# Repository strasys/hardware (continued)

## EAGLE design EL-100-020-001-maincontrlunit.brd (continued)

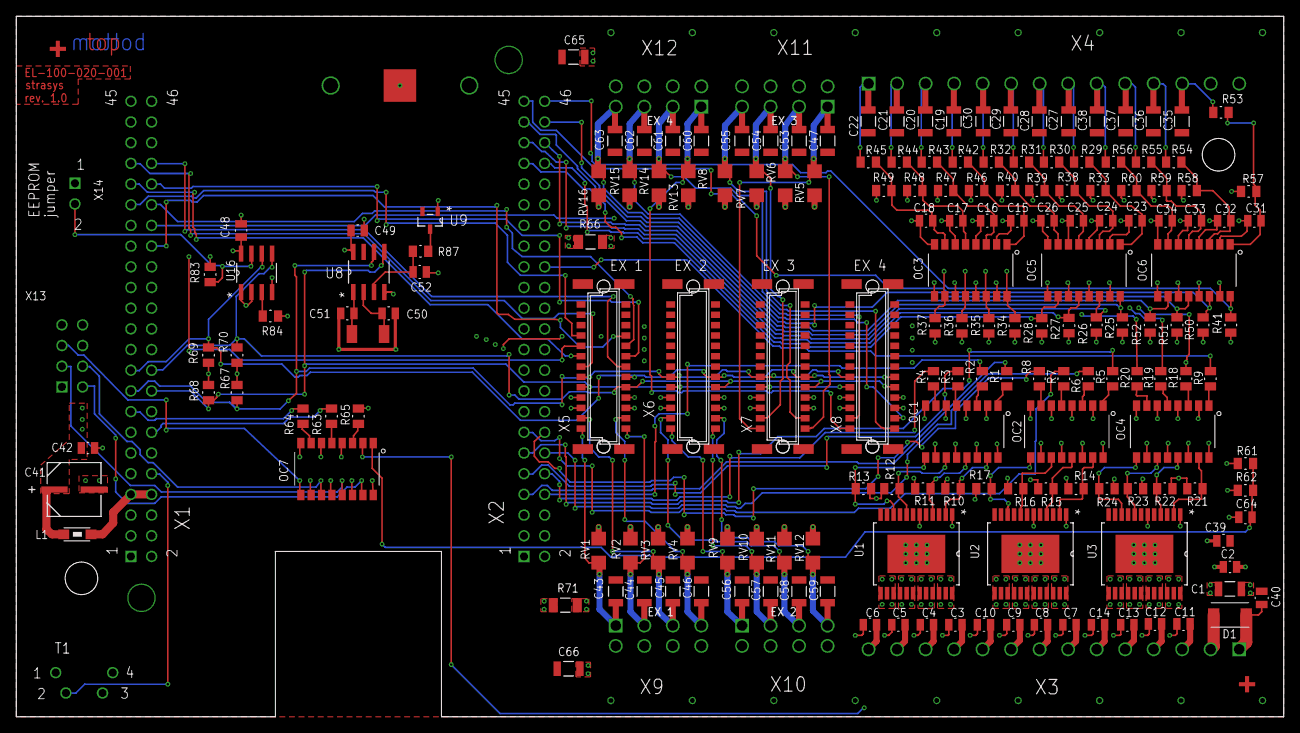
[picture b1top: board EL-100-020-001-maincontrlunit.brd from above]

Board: 4 copper layers, 155.6 x 86.0 mm, 190 parts (0 on the bottom side), 138 nets.

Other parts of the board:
U$1, U$2: PASSER_SMD4

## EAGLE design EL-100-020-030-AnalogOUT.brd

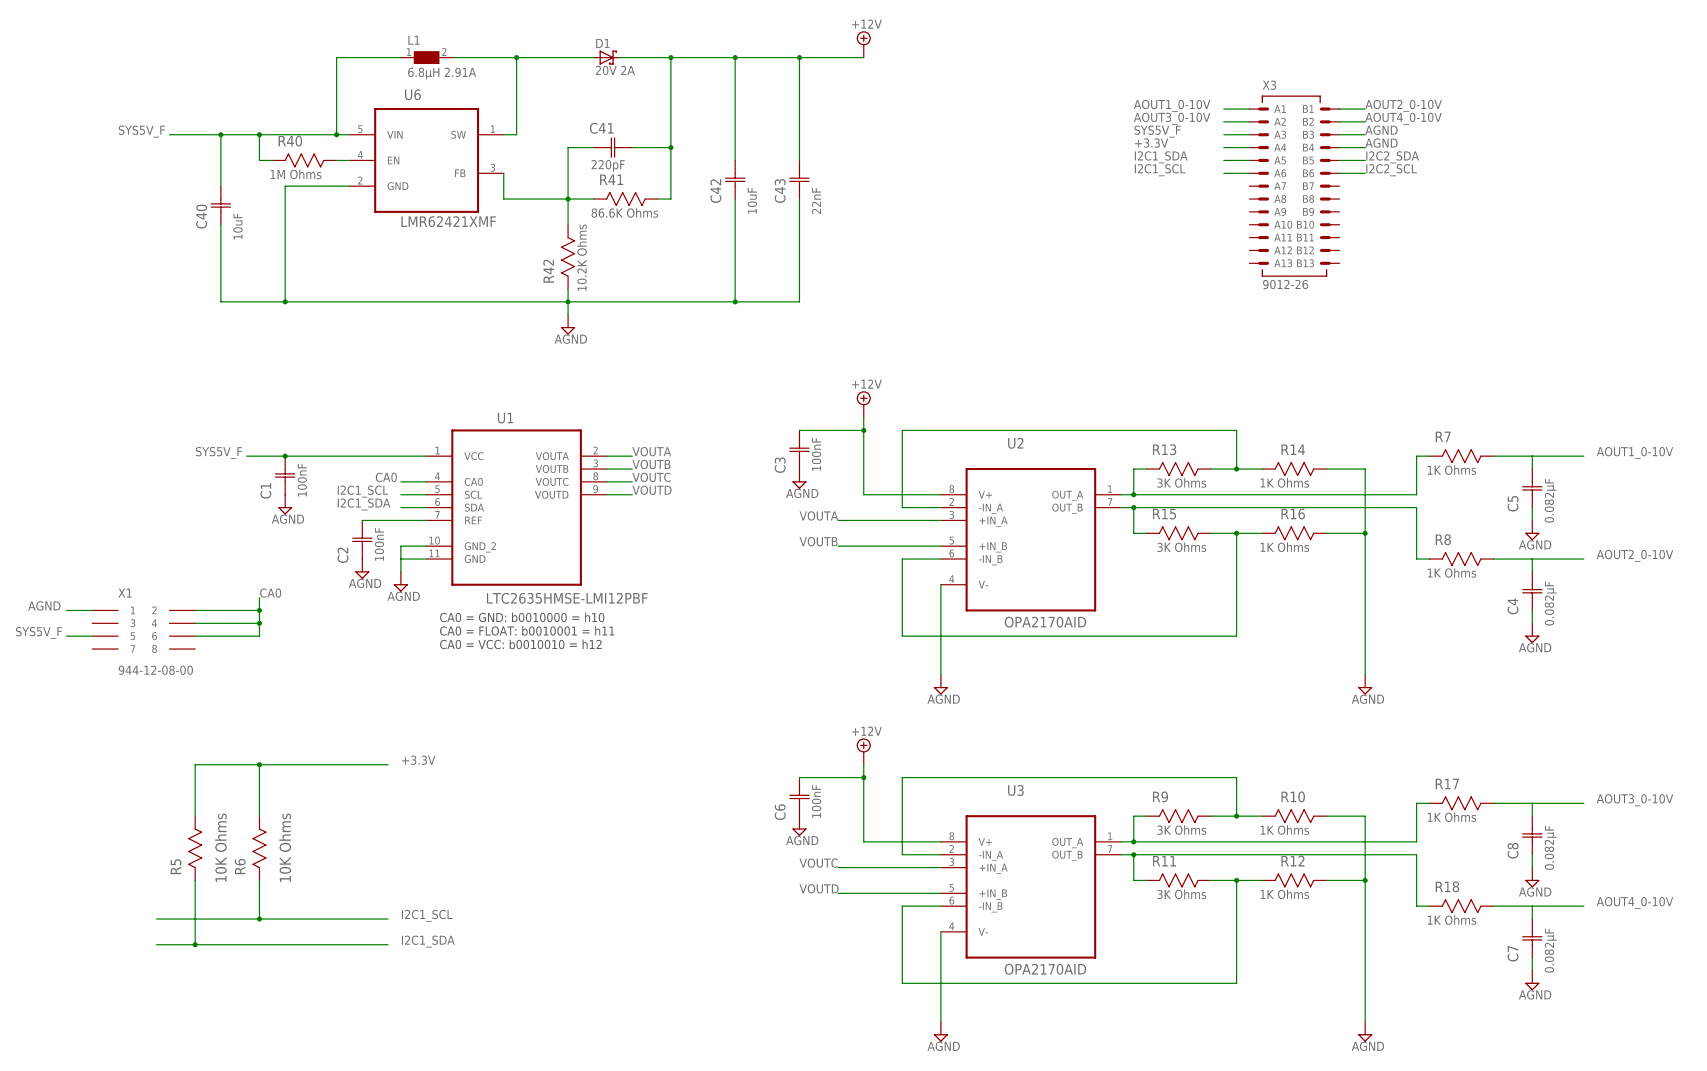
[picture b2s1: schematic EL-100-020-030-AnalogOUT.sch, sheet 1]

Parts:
C1, C2, C3, C6: 100nF; CAPC2013X110N
C4, C5, C7, C8: 0.082µF; CAPC2013X88N; TOLERANCE ±10%; MPN MC0805B823K500CT
C40: 10uF; CAPC2013X140N
C41: 220pF; CAPC2013X88N
C42: 10uF; CAPC3216X180N
C43: 22nF; CAPC2013X88N
D1: 20V 2A; SMB
L1: 6.8µH 2.91A; WE-PD_7332/7345_PLASTIC_BASE
R5, R6: 10K Ohms; RESC2013X65N
R7, R8, R17, R18: 1K Ohms; RESC2013X65N
R9, R11, R13, R15: 3K Ohms; RESC2013X65N; TOLERANCE ±0.1%; MPN ERA6AEB302V
R10, R12, R14, R16: 1K Ohms; RESC2013X65N; TOLERANCE ±0.1%; MPN ERA6AEB102V
R40: 1M Ohms; RESC2013X65N
R41: 86.6K Ohms; RESC2013X65N
R42: 10.2K Ohms; RESC2013X65N
U1: LTC2635HMSE-LMI12PBF; SOP50P490X110-11N
U2, U3: OPA2170AID; SOIC127P600X175-8N
U6: LMR62421XMF; SOT95P290X145-5N
X1: 944-12-08-00; 2,54_2X8
X3: 9012-26

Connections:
+3.3V: R5.1, R6.1, X3.A4; also elsewhere on the board
+12V: C3.2 (C2), C6.2 (C2), C41.2 (C2), C42.2 (C2), C43.2 (C2), D1.C, R41.1, U2.8 (V+), U3.8 (V+)
AGND: C1.1 (C1), C2.1 (C1), C3.1 (C1), C4.1 (C1), C5.1 (C1), C6.1 (C1), C7.1 (C1), C8.1 (C1), C40.1 (C1), C42.1 (C1), C43.1 (C1), R10.1, R12.1, R14.1, R16.1, R42.2, U1.10 (GND_2), U1.11 (GND), U2.4 (V-), U3.4 (V-), U6.2 (GND), X1.P1 (1), X3.B3, X3.B4; also elsewhere on the board
AOUT1_0-10V: C5.2 (C2), R7.1, X3.A1
AOUT2_0-10V: C4.2 (C2), R8.1, X3.B1
AOUT3_0-10V: C8.2 (C2), R17.1, X3.A2
AOUT4_0-10V: C7.2 (C2), R18.1, X3.B2
CA0: U1.4 (CA0), X1.P2 (2), X1.P4 (4), X1.P6 (6)
FB_LMR62: C41.1 (C1), R41.2, R42.1, U6.3 (FB)
I2C1_SCL: R6.2, U1.5 (SCL), X3.A6
I2C1_SDA: R5.2, U1.6 (SDA), X3.A5
I2C2_SCL: X3.B6; also elsewhere on the board
I2C2_SDA: X3.B5; also elsewhere on the board
unnamed: C2.2 (C2), U1.7 (REF)
unnamed: R40.1, U6.4 (EN)
OPA21_-IN_A: R13.1, R14.2, U2.2 (-IN_A)
OPA21_-IN_A1: R9.1, R10.2, U3.2 (-IN_A)
OPA21_-IN_B: R15.1, R16.2, U2.6 (-IN_B)
OPA21_-IN_B1: R11.1, R12.2, U3.6 (-IN_B)
OPA21_AOUTB: R8.2, R15.2, U2.7 (OUT_B)
OPA21_AOUTB1: R11.2, R18.2, U3.7 (OUT_B)
OPA21_OUT_A: R7.2, R13.2, U2.1 (OUT_A)
OPA21_OUT_A1: R9.2, R17.2, U3.1 (OUT_A)
SW_LMR62: D1.A, L1.2, U6.1 (SW)
SYS5V_F: C1.2 (C2), C40.2 (C2), L1.1, R40.2, U1.1 (VCC), U6.5 (VIN), X1.P5 (5), X3.A3
VOUTA: U1.2 (VOUTA), U2.3 (+IN_A)
VOUTB: U1.3 (VOUTB), U2.5 (+IN_B)
VOUTC: U1.8 (VOUTC), U3.3 (+IN_A)
VOUTD: U1.9 (VOUTD), U3.5 (+IN_B)

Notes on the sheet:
CA0 = GND: b0010000 = h10 CA0 = FLOAT: b0010001 = h11 CA0 = VCC: b0010010 = h12

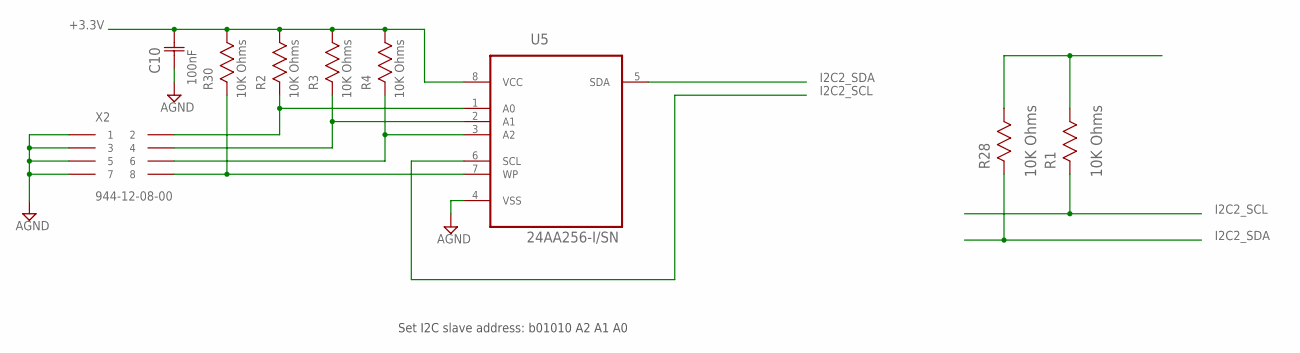
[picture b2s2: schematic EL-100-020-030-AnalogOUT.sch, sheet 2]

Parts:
C10: 100nF; CAPC2013X110N
R1, R2, R3, R4, R28, R30: 10K Ohms; RESC2013X65N
U5: 24AA256-I/SN; SOIC127P600X175-8N
X2: 944-12-08-00; 2,54_2X8

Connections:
24AA-A0: R2.2, U5.1 (A0), X2.P2 (2)
24AA_A1: R3.2, U5.2 (A1), X2.P4 (4)
24AA_A2: R4.2, U5.3 (A2), X2.P6 (6)
24AA_WP: R30.2, U5.7 (WP), X2.P8 (8)
+3.3V: C10.2 (C2), R1.1, R2.1, R3.1, R4.1, R28.1, R30.1, U5.8 (VCC); also elsewhere on the board
AGND: C10.1 (C1), U5.4 (VSS), X2.P1 (1), X2.P3 (3), X2.P5 (5), X2.P7 (7); also elsewhere on the board
I2C2_SCL: R1.2, U5.6 (SCL); also elsewhere on the board
I2C2_SDA: R28.2, U5.5 (SDA); also elsewhere on the board

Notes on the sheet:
Set I2C slave address: b01010 A2 A1 A0

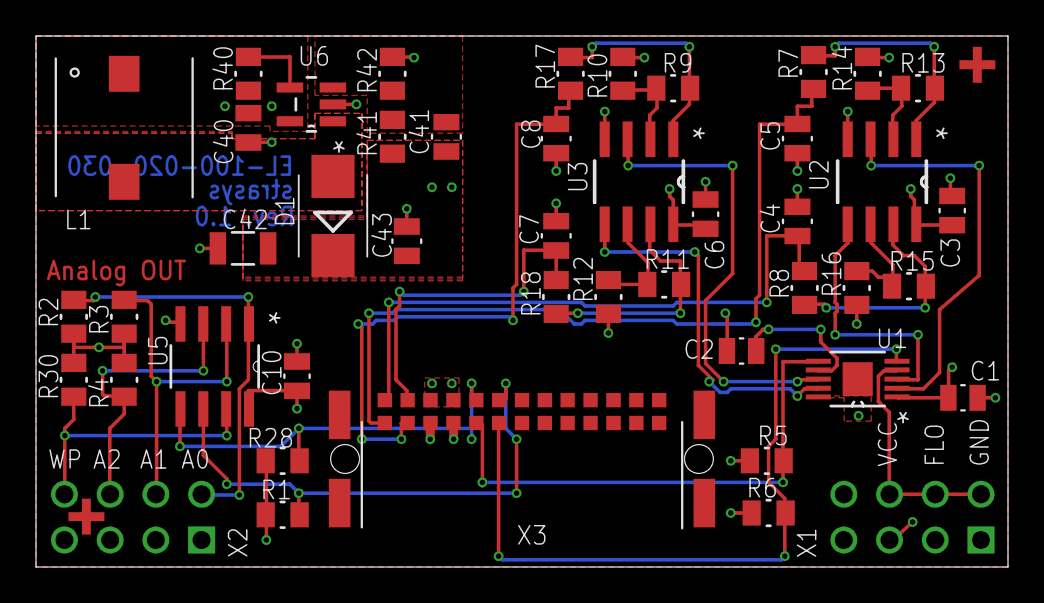
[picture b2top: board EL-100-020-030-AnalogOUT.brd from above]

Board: 4 copper layers, 54.0 x 29.5 mm, 48 parts (0 on the bottom side), 33 nets.

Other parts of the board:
U$1, U$2: PASSER_SMD4

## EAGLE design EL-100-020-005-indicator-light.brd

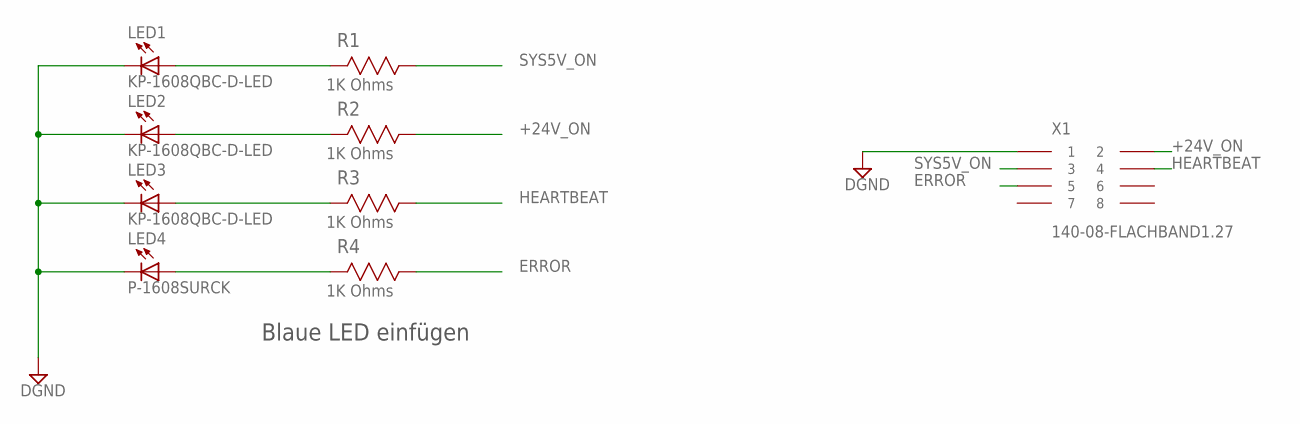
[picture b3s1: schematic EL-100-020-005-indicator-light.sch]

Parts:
LED1, LED2, LED3: KP-1608QBC-D-LED; KP-1608QBCD-D-LED
LED4: P-1608SURCK; KP-1608QBCD-D-LED
R1, R2, R3, R4: 1K Ohms; RESC2013X65N
X1: 140-08-FLACHBAND1.27; 2,54_2X8

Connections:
+24V_ON: R2.1, X1.P2 (2)
DGND: LED1.2, LED2.2, LED3.2, LED4.2, X1.P1 (1)
ERROR: R4.1, X1.P5 (5)
HEARTBEAT: R3.1, X1.P4 (4)
unnamed: LED1.1, R1.2
unnamed: LED2.1, R2.2
unnamed: LED3.1, R3.2
unnamed: LED4.1, R4.2
SYS5V_ON: R1.1, X1.P3 (3)

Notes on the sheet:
Blaue LED einfügen

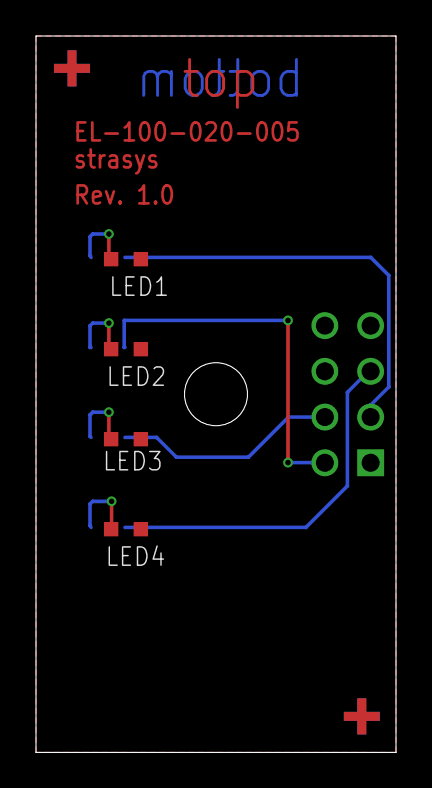
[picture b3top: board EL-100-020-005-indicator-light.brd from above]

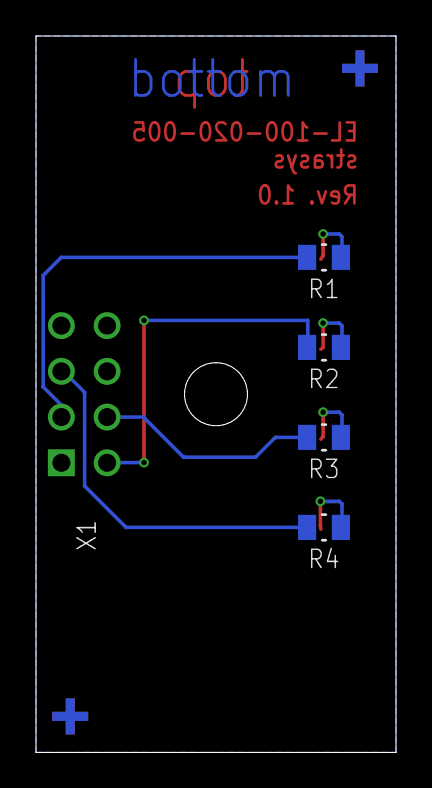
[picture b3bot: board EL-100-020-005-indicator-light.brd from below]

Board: 2 copper layers, 20.0 x 39.8 mm, 13 parts (7 on the bottom side), 9 nets.

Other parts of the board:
U$1, U$2, U$3, U$4: PASSER_SMD4

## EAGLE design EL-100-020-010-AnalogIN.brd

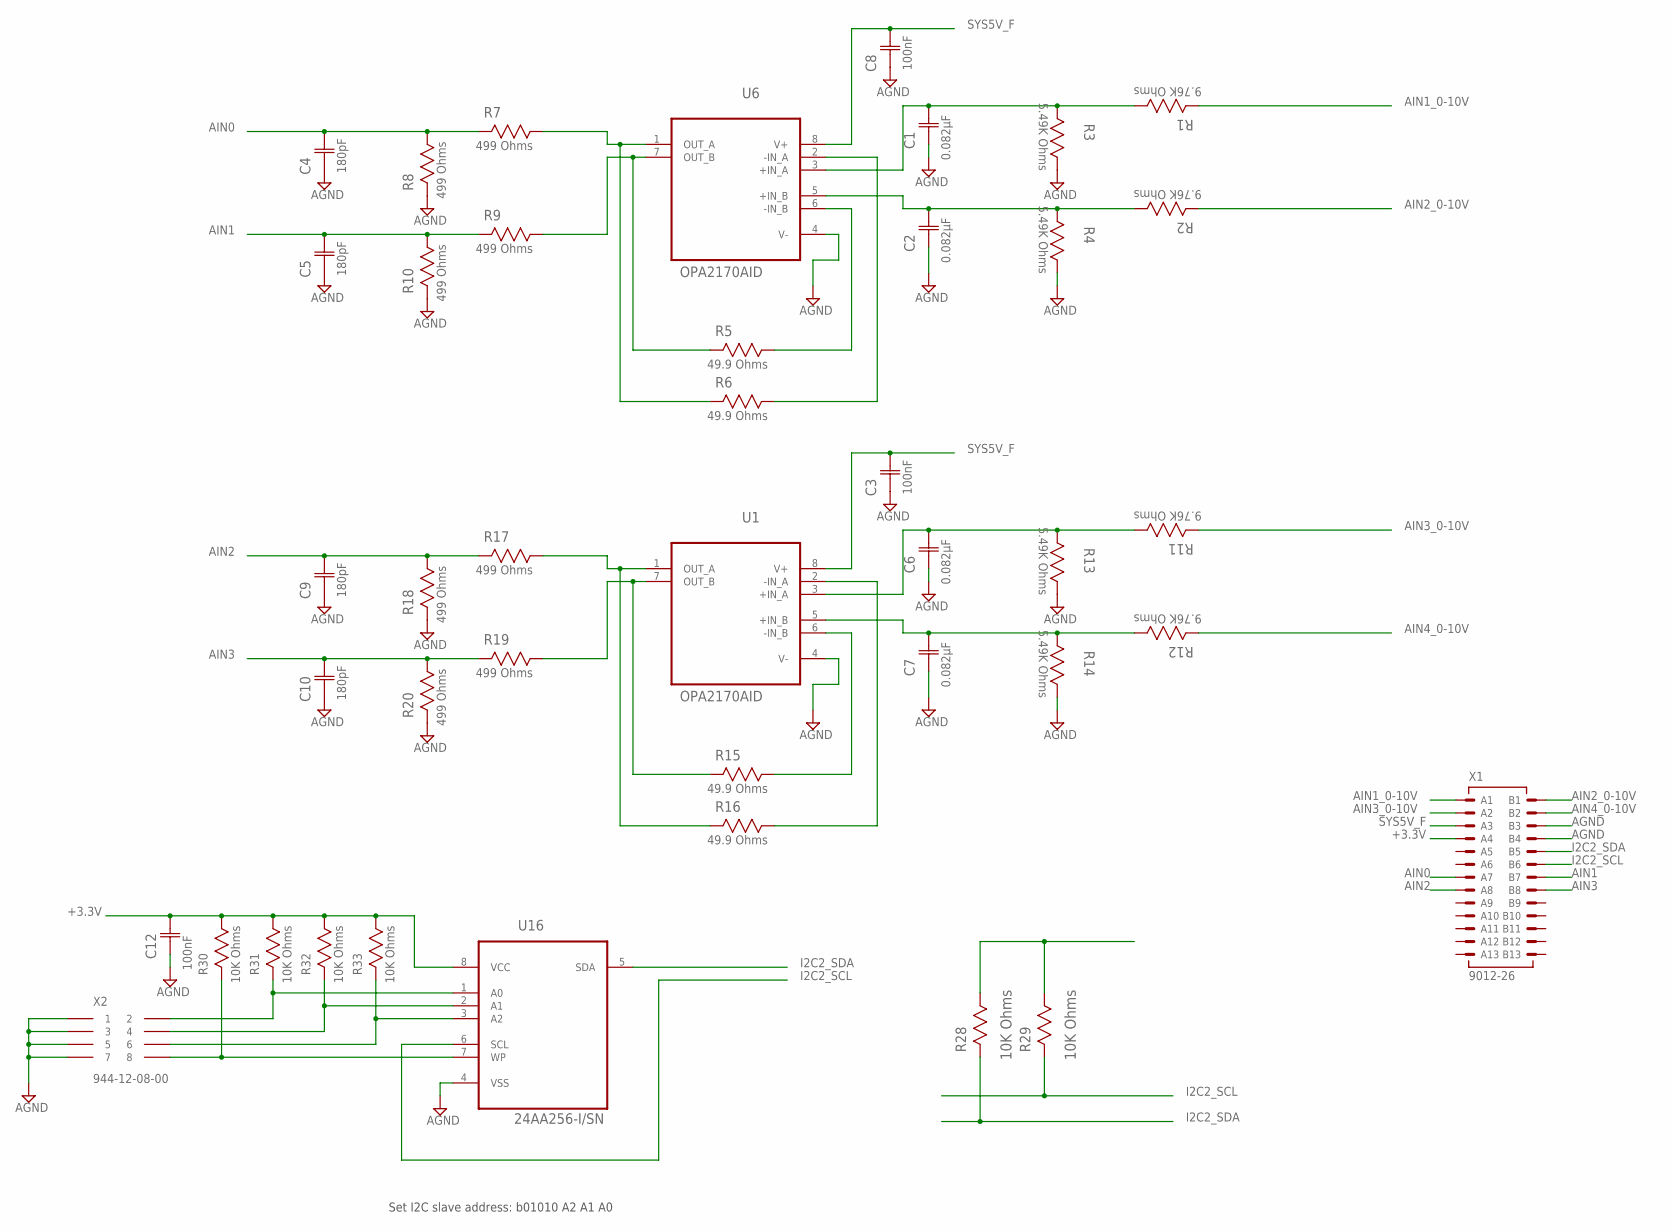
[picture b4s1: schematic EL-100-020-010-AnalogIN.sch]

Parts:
C1, C2, C6, C7: 0.082µF; CAPC2013X88N; TOLERANCE ±10%; MPN MC0805B823K500CT
C3, C8, C12: 100nF; CAPC2013X110N
C4, C5, C9, C10: 180pF; CAPC2013X88N; MPN C0805C181J5GACTU
R1, R2, R11, R12: 9.76K Ohms; RESC2013X65N; TOLERANCE ±0.1%; MPN MCTC0525B9761T5E
R3, R4, R13, R14: 5.49K Ohms; RESC2013X65N; TOLERANCE ±0.1%; MPN PCF0805R-5K49BI
R5, R6, R15, R16: 49.9 Ohms; RESC2013X65N; TOLERANCE ±0.1%; MPN MCTC0525B499JT5E
R7, R8, R9, R10, R17, R18, R19, R20: 499 Ohms; RESC2013X65N; TOLERANCE ±0.1%; MPN ERA6AEB4990V
R28, R29, R30, R31, R32, R33: 10K Ohms; RESC2013X65N
U1, U6: OPA2170AID; SOIC127P600X175-8N
U16: 24AA256-I/SN; SOIC127P600X175-8N
X1: 9012-26
X2: 944-12-08-00; 2,54_2X8

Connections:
24AA-A0: R31.2, U16.1 (A0), X2.P2 (2)
24AA_A1: R32.2, U16.2 (A1), X2.P4 (4)
24AA_A2: R33.2, U16.3 (A2), X2.P6 (6)
24AA_WP: R30.2, U16.7 (WP), X2.P8 (8)
+3.3V: C12.2 (C2), R28.1, R29.1, R30.1, R31.1, R32.1, R33.1, U16.8 (VCC), X1.A4
AGND: C1.1 (C1), C2.1 (C1), C3.1 (C1), C4.1 (C1), C5.1 (C1), C6.1 (C1), C7.1 (C1), C8.1 (C1), C9.1 (C1), C10.1 (C1), C12.1 (C1), R3.1, R4.1, R8.2, R10.2, R13.1, R14.1, R18.2, R20.2, U1.4 (V-), U6.4 (V-), U16.4 (VSS), X1.B3, X1.B4, X2.P1 (1), X2.P3 (3), X2.P5 (5), X2.P7 (7)
AIN0: C4.2 (C2), R7.2, R8.1, X1.A7
AIN1: C5.2 (C2), R9.2, R10.1, X1.B7
AIN1_0-10V: R1.2, X1.A1
AIN2: C9.2 (C2), R17.2, R18.1, X1.A8
AIN2_0-10V: R2.2, X1.B1
AIN3: C10.2 (C2), R19.2, R20.1, X1.B8
AIN3_0-10V: R11.2, X1.A2
AIN4_0-10V: R12.2, X1.B2
I2C2_SCL: R29.2, U16.6 (SCL), X1.B6
I2C2_SDA: R28.2, U16.5 (SDA), X1.B5
unnamed: C6.2 (C2), R11.1, R13.2, U1.3 (+IN_A)
unnamed: C7.2 (C2), R12.1, R14.2, U1.5 (+IN_B)
unnamed: C1.2 (C2), R1.1, R3.2, U6.3 (+IN_A)
unnamed: C2.2 (C2), R2.1, R4.2, U6.5 (+IN_B)
OPA2170_-IN_A_1: R16.1, U1.2 (-IN_A)
OPA2170_-IN_A_2: R6.1, U6.2 (-IN_A)
OPA2170_-IN_B_1: R15.1, U1.6 (-IN_B)
OPA2170_-IN_B_2: R5.1, U6.6 (-IN_B)
OPA2170_OUT_A_1: R16.2, R17.1, U1.1 (OUT_A)
OPA2170_OUT_A_2: R6.2, R7.1, U6.1 (OUT_A)
OPA2170_OUT_B_1: R15.2, R19.1, U1.7 (OUT_B)
OPA2170_OUT_B_2: R5.2, R9.1, U6.7 (OUT_B)
SYS5V_F: C3.2 (C2), C8.2 (C2), U1.8 (V+), U6.8 (V+), X1.A3

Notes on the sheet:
Set I2C slave address: b01010 A2 A1 A0

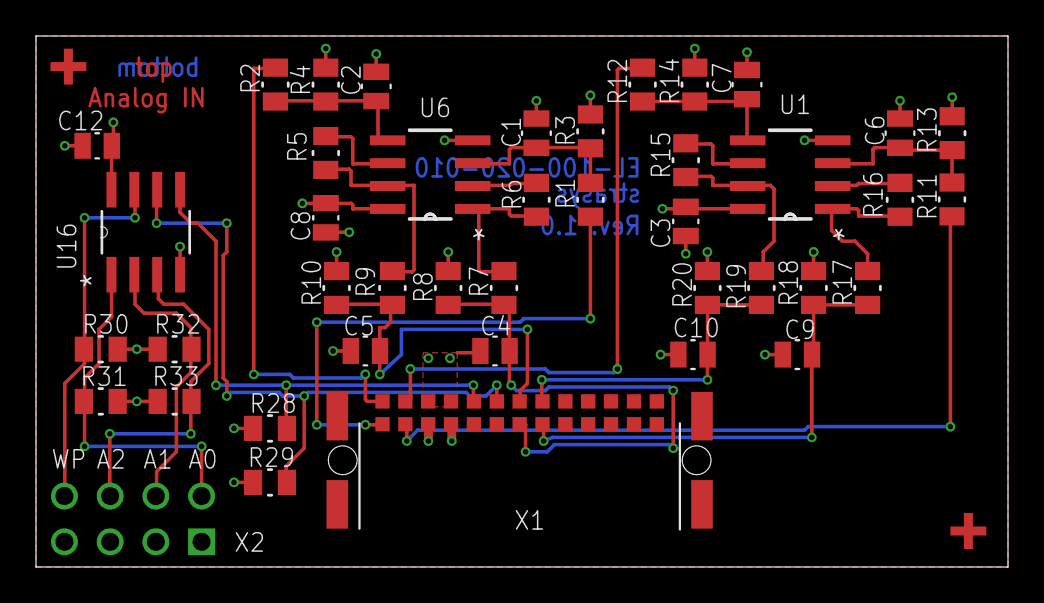
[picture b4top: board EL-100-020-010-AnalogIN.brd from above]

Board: 4 copper layers, 54.0 x 29.5 mm, 44 parts (0 on the bottom side), 29 nets.

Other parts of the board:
U$1, U$2: PASSER_SMD4

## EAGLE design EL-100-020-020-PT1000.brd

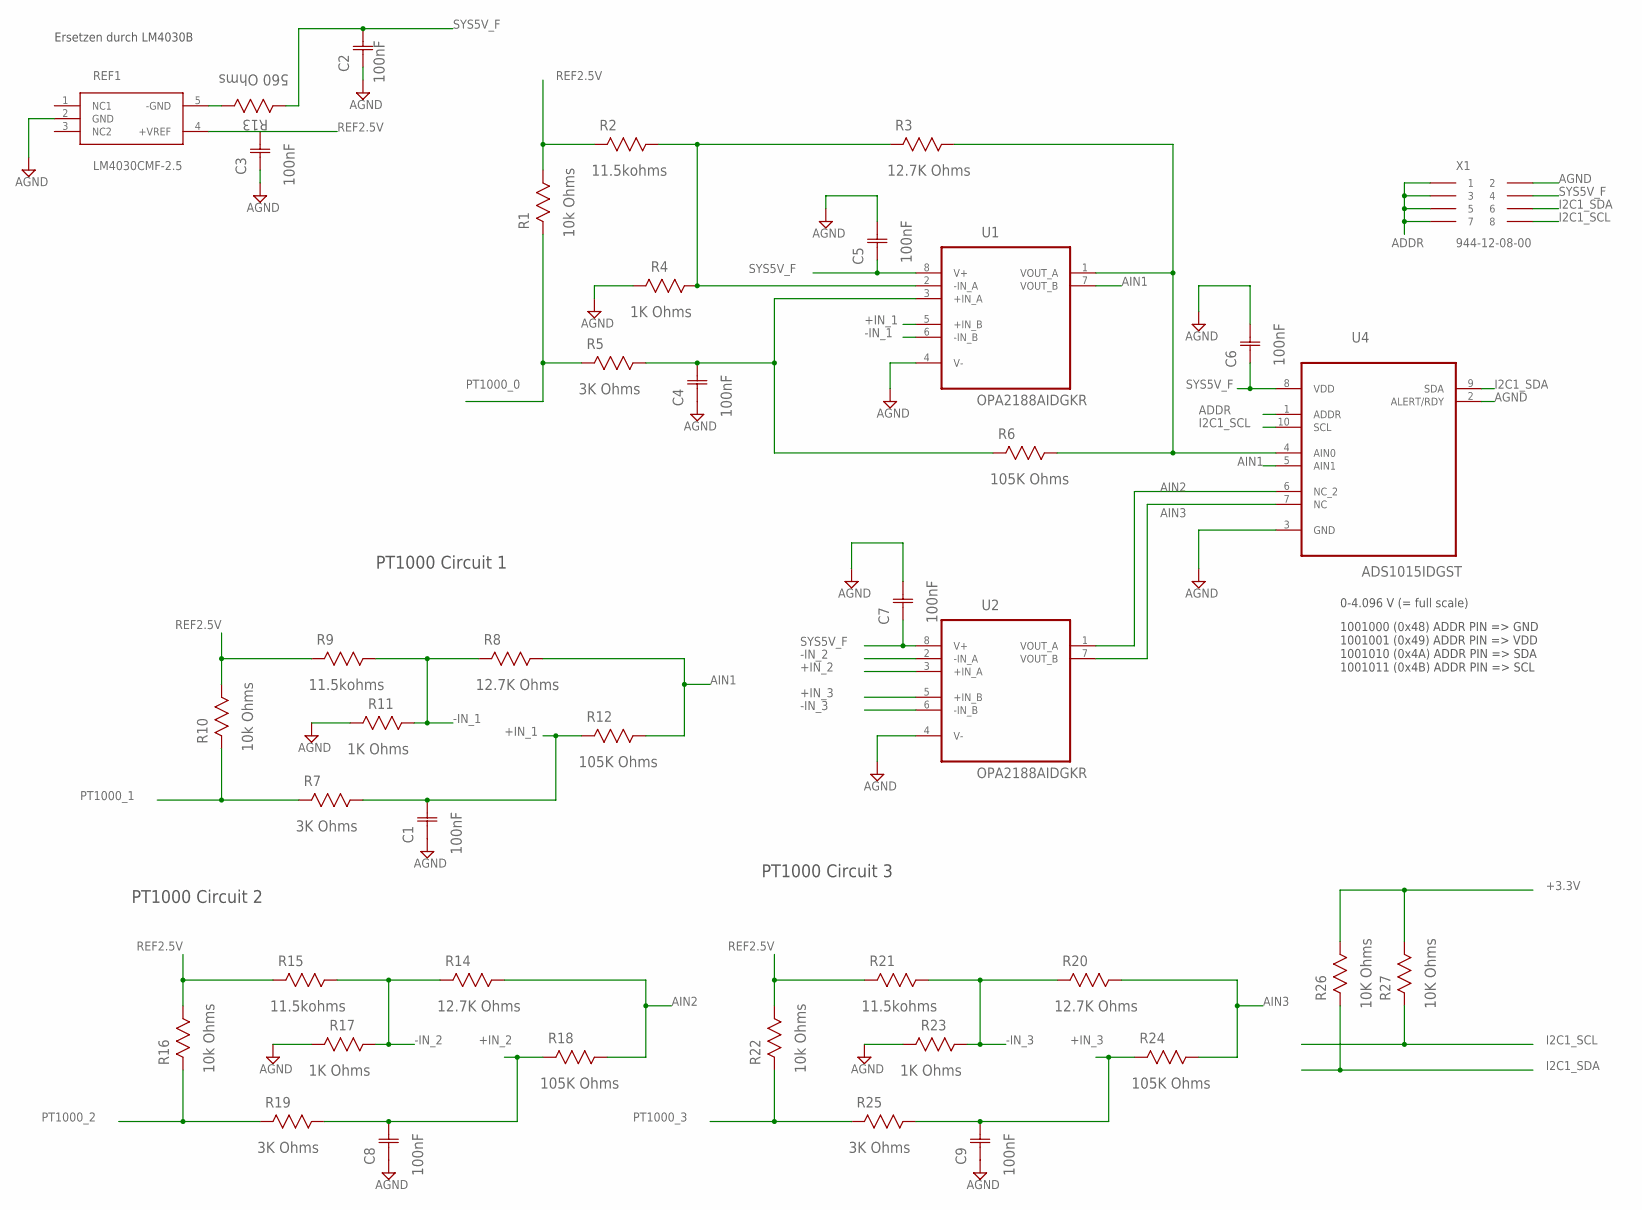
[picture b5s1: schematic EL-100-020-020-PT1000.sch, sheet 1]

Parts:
C1, C2, C3, C4, C5, C6, C7, C8, C9: 100nF; CAPC2013X110N
R1, R10, R16, R22: 10k Ohms; RESC2013X65N; TOLERANCE ±0.1%; MPN ERA6AEB103V
R2, R9, R15, R21: 11.5kohms; RESC2013X65N; TOLERANCE +/- 0.1%; MPN MCTC0525B1152T5E
R3, R8, R14, R20: 12.7K Ohms; RESC2013X65N; TOLERANCE ±0.1%; MPN MCTC0525B1272T5E
R4, R11, R17, R23: 1K Ohms; RESC2013X65N; TOLERANCE ±0.1%; MPN ERA6AEB102V
R5, R7, R19, R25: 3K Ohms; RESC2013X65N; TOLERANCE ±0.1%; MPN ERA6AEB302V
R6, R12, R18, R24: 105K Ohms; RESC2013X65N; TOLERANCE ±0.1%; MPN MCTC0525B1053T5E
R13: 560 Ohms; RESC2013X65N; MPN MCMR08X561 JTL
R26, R27: 10K Ohms; RESC2013X65N
REF1: LM4030CMF-2.5; R-PDSO-G5
U1, U2: OPA2188AIDGKR; SOP65P490X110-8N
U4: ADS1015IDGST; SOP50P490X110-10N
X1: 944-12-08-00; 2,54_2X8

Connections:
+3.3V: R26.1, R27.1; also elsewhere on the board
+IN_0: C4.2 (C2), R5.1, R6.2, U1.3 (+IN_A)
+IN_1: C1.2 (C2), R7.1, R12.2, U1.5 (+IN_B)
+IN_2: C8.2 (C2), R18.2, R19.1, U2.3 (+IN_A)
+IN_3: C9.2 (C2), R24.2, R25.1, U2.5 (+IN_B)
-IN_0: R2.1, R3.2, R4.1, U1.2 (-IN_A)
-IN_1: R8.2, R9.1, R11.1, U1.6 (-IN_B)
-IN_2: R14.2, R15.1, R17.1, U2.2 (-IN_A)
-IN_3: R20.2, R21.1, R23.1, U2.6 (-IN_B)
ADDR: U4.1 (ADDR), X1.P1 (1), X1.P3 (3), X1.P5 (5), X1.P7 (7)
AGND: C1.1 (C1), C2.1 (C1), C3.1 (C1), C4.1 (C1), C5.2 (C2), C6.2 (C2), C7.2 (C2), C8.1 (C1), C9.1 (C1), R4.2, R11.2, R17.2, R23.2, REF1.2 (GND), U1.4 (V-), U2.4 (V-), U4.2 (ALERT/RDY), U4.3 (GND), X1.P2 (2); also elsewhere on the board
AIN0: R3.1, R6.1, U1.1 (VOUT_A), U4.4 (AIN0)
AIN1: R8.1, R12.1, U1.7 (VOUT_B), U4.5 (AIN1)
AIN2: R14.1, R18.1, U2.1 (VOUT_A), U4.6 (NC_2)
AIN3: R20.1, R24.1, U2.7 (VOUT_B), U4.7 (NC)
I2C1_SCL: R27.2, U4.10 (SCL), X1.P8 (8); also elsewhere on the board
I2C1_SDA: R26.2, U4.9 (SDA), X1.P6 (6); also elsewhere on the board
unnamed: R13.1, REF1.5 (-GND)
PT1000_0: R1.2, R5.2; also elsewhere on the board
PT1000_1: R7.2, R10.2; also elsewhere on the board
PT1000_2: R16.2, R19.2; also elsewhere on the board
PT1000_3: R22.2, R25.2; also elsewhere on the board
REF2.5V: C3.2 (C2), R1.1, R2.2, R9.2, R10.1, R15.2, R16.1, R21.2, R22.1, REF1.4 (+VREF)
SYS5V_F: C2.2 (C2), C5.1 (C1), C6.1 (C1), C7.1 (C1), R13.2, U1.8 (V+), U2.8 (V+), U4.8 (VDD), X1.P4 (4); also elsewhere on the board

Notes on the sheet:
0-4.096 V (= full scale)
PT1000 Circuit 1
PT1000 Circuit 2
PT1000 Circuit 3
Ersetzen durch LM4030B
1001000 (0x48) ADDR PIN => GND 1001001 (0x49) ADDR PIN => VDD 1001010 (0x4A) ADDR PIN => SDA 1001011 (0x4B) ADDR PIN => SCL

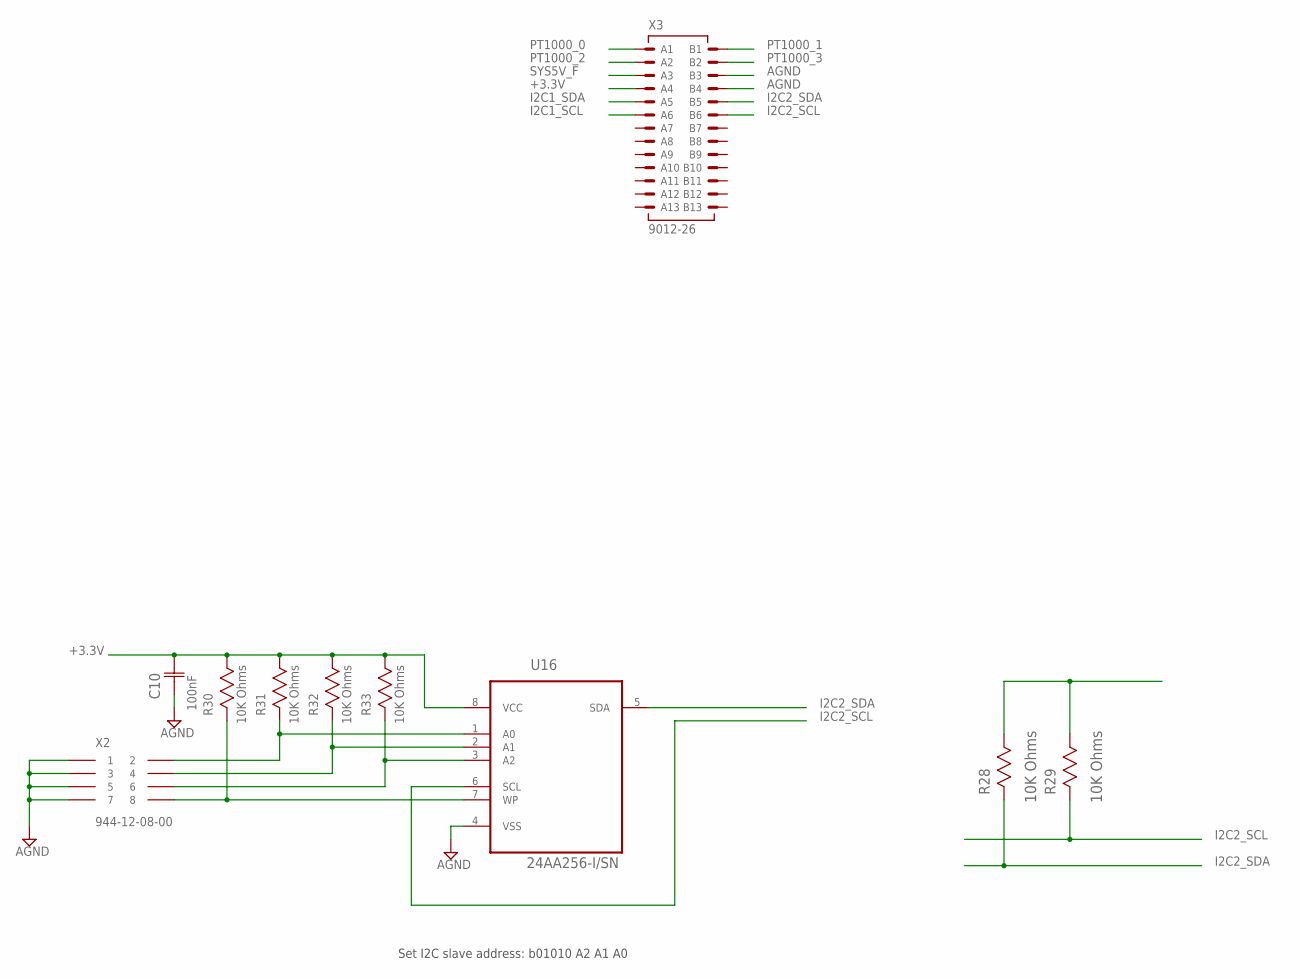
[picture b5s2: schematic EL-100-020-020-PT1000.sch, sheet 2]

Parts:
C10: 100nF; CAPC2013X110N
R28, R29, R30, R31, R32, R33: 10K Ohms; RESC2013X65N
U16: 24AA256-I/SN; SOIC127P600X175-8N
X2: 944-12-08-00; 2,54_2X8
X3: 9012-26

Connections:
24AA-A0: R31.2, U16.1 (A0), X2.P2 (2)
24AA_A1: R32.2, U16.2 (A1), X2.P4 (4)
24AA_A2: R33.2, U16.3 (A2), X2.P6 (6)
24AA_WP: R30.2, U16.7 (WP), X2.P8 (8)
+3.3V: C10.2 (C2), R28.1, R29.1, R30.1, R31.1, R32.1, R33.1, U16.8 (VCC), X3.A4; also elsewhere on the board
AGND: C10.1 (C1), U16.4 (VSS), X2.P1 (1), X2.P3 (3), X2.P5 (5), X2.P7 (7), X3.B3, X3.B4; also elsewhere on the board
I2C1_SCL: X3.A6; also elsewhere on the board
I2C1_SDA: X3.A5; also elsewhere on the board
I2C2_SCL: R29.2, U16.6 (SCL), X3.B6
I2C2_SDA: R28.2, U16.5 (SDA), X3.B5
PT1000_0: X3.A1; also elsewhere on the board
PT1000_1: X3.B1; also elsewhere on the board
PT1000_2: X3.A2; also elsewhere on the board
PT1000_3: X3.B2; also elsewhere on the board
SYS5V_F: X3.A3; also elsewhere on the board

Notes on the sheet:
Set I2C slave address: b01010 A2 A1 A0

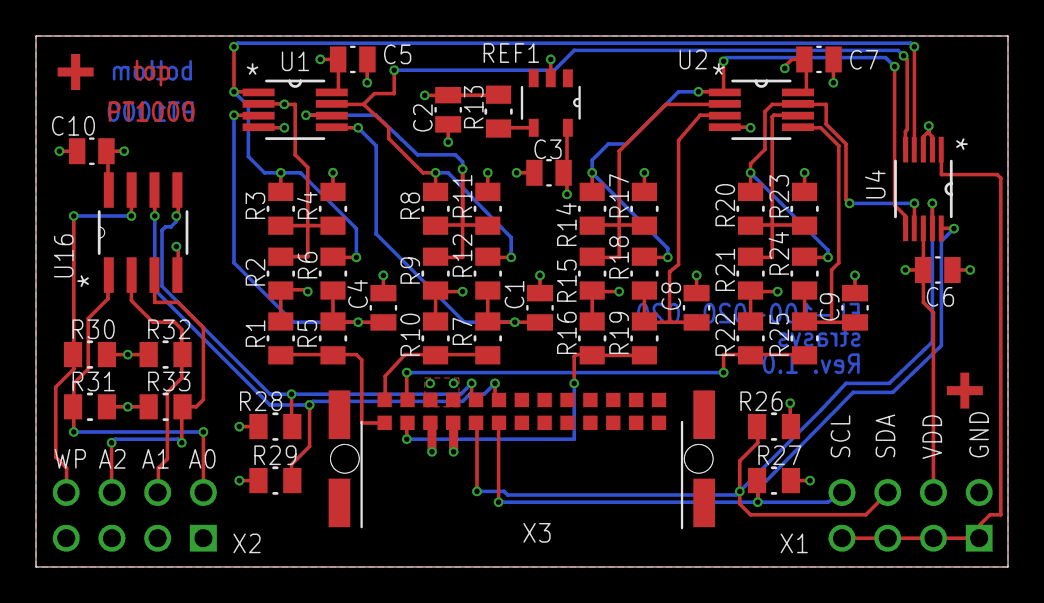
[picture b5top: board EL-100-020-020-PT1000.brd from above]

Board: 4 copper layers, 54.0 x 29.5 mm, 53 parts (0 on the bottom side), 30 nets.

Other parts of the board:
U$1, U$2: PASSER_SMD4

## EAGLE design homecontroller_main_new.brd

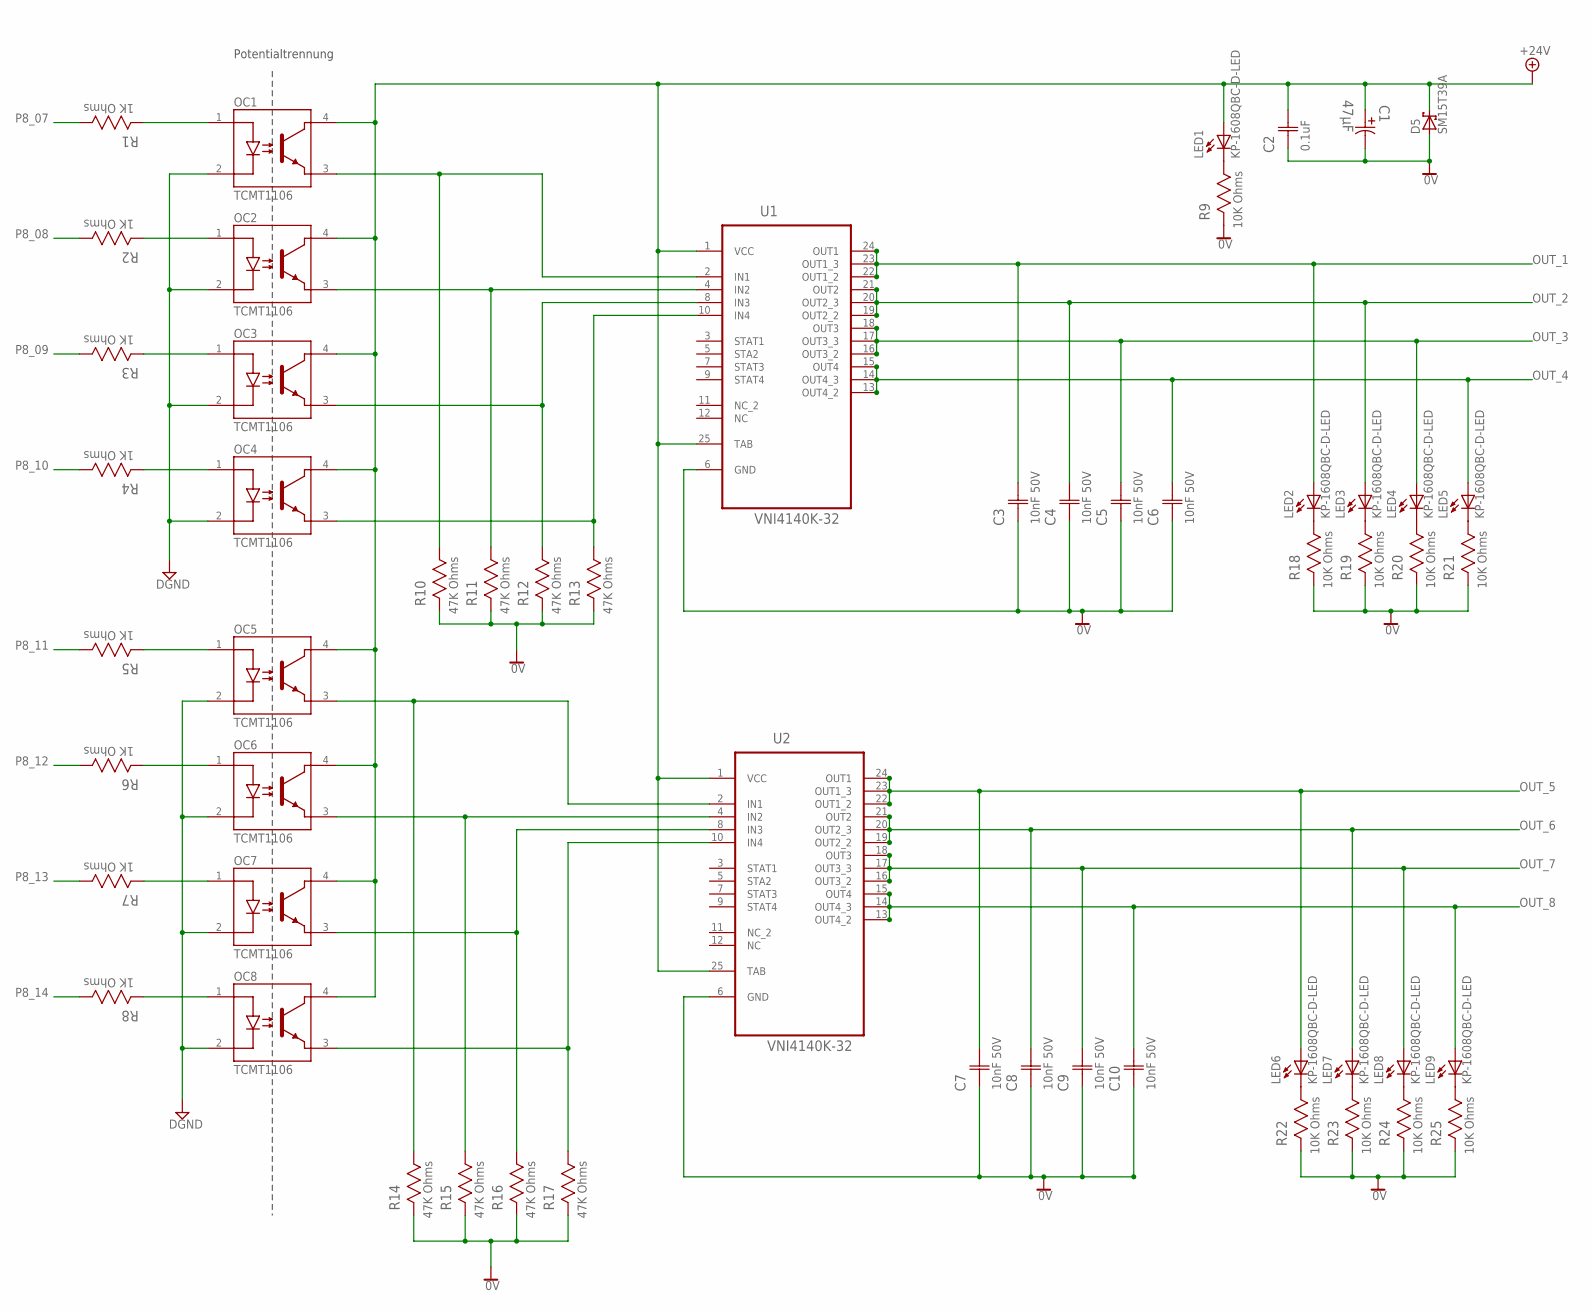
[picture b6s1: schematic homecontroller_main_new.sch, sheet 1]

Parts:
C1: 47µF; CAPAE830X650N; MPN EEEFK1H470P
C2: 0.1uF; CAPC1608X85N; MPN C0603C104K5RACTU
C3, C4, C5, C6, C7, C8, C9, C10: 10nF 50V; CAPC1608X85N
D5: SM15T39A
LED1, LED2, LED3, LED4, LED5, LED6, LED7, LED8, LED9: KP-1608QBC-D-LED; KP-1608QBCD-D-LED; MPN KP-1608QBC-D
OC1, OC2, OC3, OC4, OC5, OC6, OC7, OC8: TCMT1106; SOP-4
R1, R2, R3, R4, R5, R6, R7, R8: 1K Ohms; RESC1608X60N
R9, R18, R19, R20, R21, R22, R23, R24, R25: 10K Ohms; RESC1608X60N
R10, R11, R12, R13, R14, R15, R16, R17: 47K Ohms; RESC1608X60N
U1, U2: VNI4140K-32; SOP80P1030X247-25N

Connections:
0V: C1.2, C2.1 (C1), C3.1 (C1), C4.1 (C1), C5.1 (C1), C6.1 (C1), C7.1 (C1), C8.1 (C1), C9.1 (C1), C10.1 (C1), D5.A, R9.2, R10.2, R11.2, R12.2, R13.2, R14.2, R15.2, R16.2, R17.2, R18.2, R19.2, R20.2, R21.2, R22.2, R23.2, R24.2, R25.2, U1.6 (GND), U2.6 (GND); also elsewhere on the board
+24V: C1.1, C2.2 (C2), D5.K (C), LED1.1, OC1.4, OC2.4, OC3.4, OC4.4, OC5.4, OC6.4, OC7.4, OC8.4, U1.1 (VCC), U1.25 (TAB), U2.1 (VCC), U2.25 (TAB); also elsewhere on the board
DGND: OC1.2, OC2.2, OC3.2, OC4.2, OC5.2, OC6.2, OC7.2, OC8.2; also elsewhere on the board
unnamed: LED2.2, R18.1
unnamed: LED3.2, R19.1
unnamed: LED4.2, R20.1
unnamed: LED5.2, R21.1
unnamed: LED6.2, R22.1
unnamed: LED7.2, R23.1
unnamed: LED8.2, R24.1
unnamed: LED9.2, R25.1
unnamed: OC1.3, R10.1, U1.2 (IN1)
unnamed: OC1.1, R1.2
unnamed: OC2.1, R2.2
unnamed: OC3.1, R3.2
unnamed: OC4.1, R4.2
unnamed: LED1.2, R9.1
unnamed: OC2.3, R11.1, U1.4 (IN2)
unnamed: OC3.3, R12.1, U1.8 (IN3)
unnamed: OC4.3, R13.1, U1.10 (IN4)
unnamed: OC5.1, R5.2
unnamed: OC6.1, R6.2
unnamed: OC7.1, R7.2
unnamed: OC8.1, R8.2
unnamed: OC5.3, R14.1, U2.2 (IN1)
unnamed: OC6.3, R15.1, U2.4 (IN2)
unnamed: OC7.3, R16.1, U2.8 (IN3)
unnamed: OC8.3, R17.1, U2.10 (IN4)
OUT_1: C3.2 (C2), LED2.1, U1.22 (OUT1_2), U1.23 (OUT1_3), U1.24 (OUT1); also elsewhere on the board
OUT_2: C4.2 (C2), LED3.1, U1.19 (OUT2_2), U1.20 (OUT2_3), U1.21 (OUT2); also elsewhere on the board
OUT_3: C5.2 (C2), LED4.1, U1.16 (OUT3_2), U1.17 (OUT3_3), U1.18 (OUT3); also elsewhere on the board
OUT_4: C6.2 (C2), LED5.1, U1.13 (OUT4_2), U1.14 (OUT4_3), U1.15 (OUT4); also elsewhere on the board
OUT_5: C7.2 (C2), LED6.1, U2.22 (OUT1_2), U2.23 (OUT1_3), U2.24 (OUT1); also elsewhere on the board
OUT_6: C8.2 (C2), LED7.1, U2.19 (OUT2_2), U2.20 (OUT2_3), U2.21 (OUT2); also elsewhere on the board
OUT_7: C9.2 (C2), LED8.1, U2.16 (OUT3_2), U2.17 (OUT3_3), U2.18 (OUT3); also elsewhere on the board
OUT_8: C10.2 (C2), LED9.1, U2.13 (OUT4_2), U2.14 (OUT4_3), U2.15 (OUT4); also elsewhere on the board
P8_07: R1.1; also elsewhere on the board
P8_08: R2.1; also elsewhere on the board
P8_09: R3.1; also elsewhere on the board
P8_10: R4.1; also elsewhere on the board
P8_11: R5.1; also elsewhere on the board
P8_12: R6.1; also elsewhere on the board
P8_13: R7.1; also elsewhere on the board
P8_14: R8.1; also elsewhere on the board

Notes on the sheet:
Potentialtrennung
